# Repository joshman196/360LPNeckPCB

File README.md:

# 360LPNeckPCB
A functional clone of the Guitar Hero Les Paul Neck Connector PCB (for the Xbox 360 version). Before you decide to replace your original board, you can try adding solder to its worn pads to see if that will fix your issue of the fret buttons not working properly. This means you won't have to order a new PCB if that ended up being the problem.

**As this is a clone, this PCB is subject to the exact same design flaw as the original, where the pogo pins cause a "divot" on the pads which creates uneven contact, therefore making the connection unstable.** You should only use this if your PCB is beyond broken or missing, or if you want the absolute simplest/cheapest replacement. I have designed alternative neck/body connection PCBs that use pin headers instead of the old pogo pins [here](https://github.com/joshman196/360LesPaulPCB-PinHeaderVariant), which you should maybe consider if you want less problems with your Les Paul neck connection.

**SET PCB THICKNESS TO 1.2MM ON THE PCB ORDER PAGE**. Optionally on JLCPCB, you can set "Remove Order Number" to "Specify a location".

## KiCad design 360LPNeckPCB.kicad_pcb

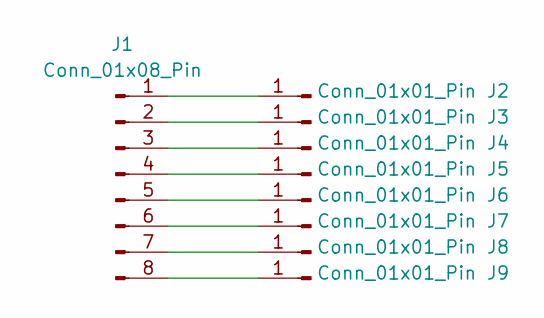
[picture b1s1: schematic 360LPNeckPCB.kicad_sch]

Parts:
J1: Conn_01x08_Pin; 1x08GHLPNeck
J2, J3, J4, J5, J6, J7, J8, J9: Conn_01x01_Pin; TestPoint_Pad_D2.5mm

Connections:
unnamed: J1.1, J2.1
unnamed: J1.2, J3.1
unnamed: J1.3, J4.1
unnamed: J1.4, J5.1
unnamed: J1.5, J6.1
unnamed: J1.6, J7.1
unnamed: J1.7, J8.1
unnamed: J1.8, J9.1

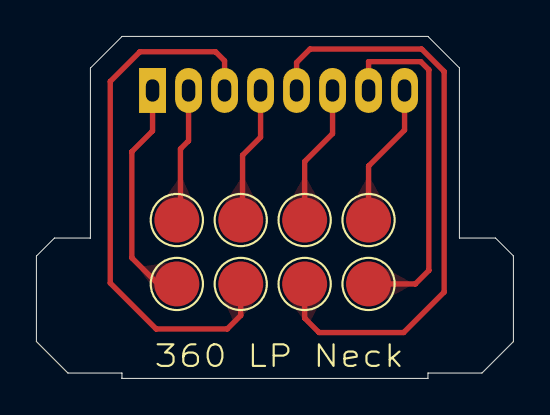
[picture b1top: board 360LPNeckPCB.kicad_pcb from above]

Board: 2 copper layers, 26.5 x 19.0 mm, 9 parts (0 on the bottom side), 8 nets.

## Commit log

2024-06-28 initial upload of all files
2026-02-12 junk
